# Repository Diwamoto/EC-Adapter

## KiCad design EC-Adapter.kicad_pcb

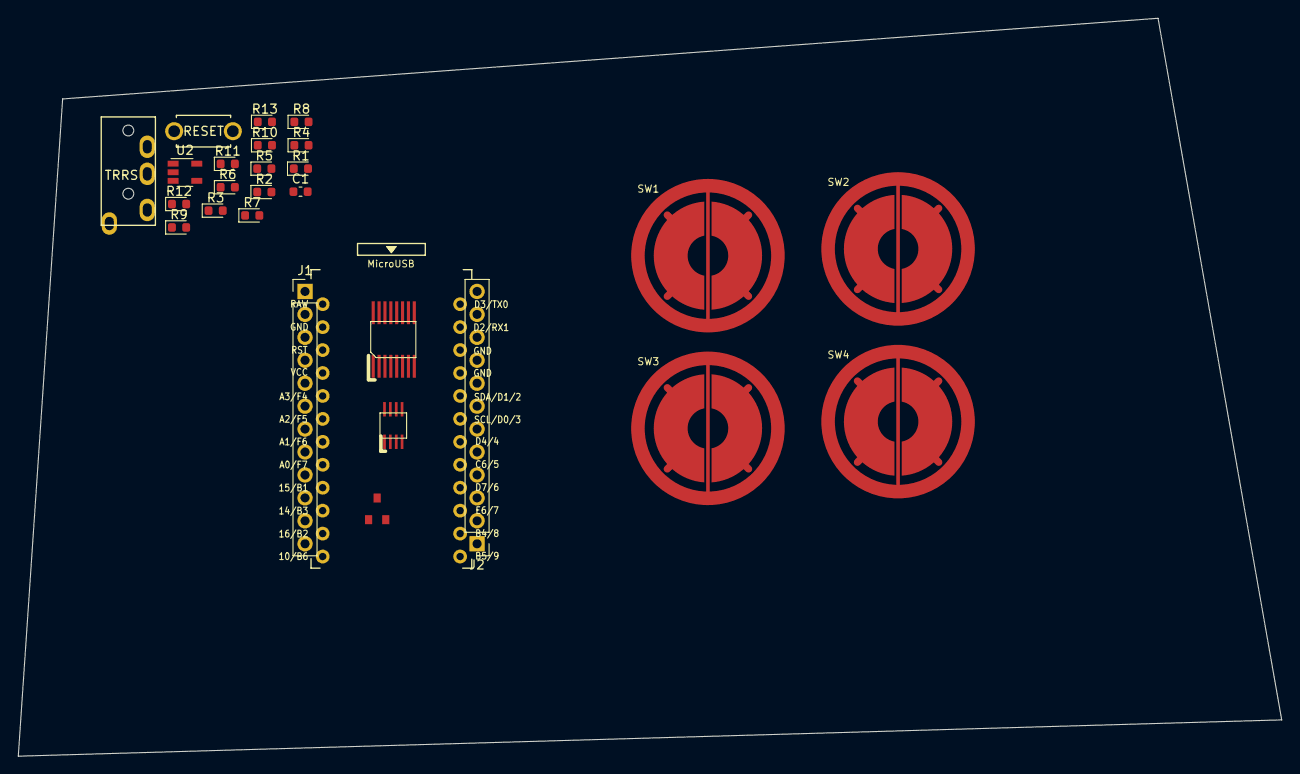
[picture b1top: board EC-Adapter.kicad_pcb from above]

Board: 2 copper layers, 139.9 x 81.7 mm, 27 parts (0 on the bottom side), 24 nets, no tracks yet.

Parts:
C1: 220pF; C_0603_1608Metric
J1, J2: Conn_01x12_Male; PinHeader_1x12_P2.54mm_Vertical
J3: MJ-4PP-9; MJ-4PP-9_1side
Q1: 2SC1941; 2SC2712
R1, R2: 10kΩ; D_0603_1608Metric
R3, R4: 1KΩ; D_0603_1608Metric
R5: 10KΩ; D_0603_1608Metric
R6: 100KΩ; D_0603_1608Metric
R7, R8, R9, R10, R11, R12, R13: 100kΩ; D_0603_1608Metric
SW1: RESET; ResetSW_1side
SW1#2, SW2, SW3, SW4: EC_SW; ec_pad_led2
U1: ProMicro; ProMicro_v3.5
U2: AD8616; TSOT-23-5
U2#2: LTC6228xS6; MSOP8
U3: 74HC4051; SSOP16

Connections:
GND: C1.2, J1.2, J2.9, J2.10, J3.C, Q1.1, R4.1, R7.2, R8.2, R9.2, R10.2, R11.2, R12.2, R13.2, SW1.2, U1.3, U1.4, U1.23, U2.2, U3.4, U3.6, U3.7, U3.8
GNDA: SW1#2.3, SW2.3, SW3.3, SW4.3
unnamed: Q1.2, R2.2
unnamed: Q1.3, R1.2
unnamed: R3.1, U2.3
unnamed: R4.2, R6.2, U2.4
unnamed: R7.1, U3.13
unnamed: R8.1, U3.14
unnamed: R9.1, U3.15
unnamed: R10.1, U3.12
unnamed: R11.1, U3.1
unnamed: R12.1, U3.5
unnamed: R13.1, U3.2
VCC: J1.4, J3.D, R5.2, U1.21, U2.5
a: C1.1, R2.1, R3.2
adc: R5.1, R6.1, U1.13, U2.1
charge: R1.1, U1.14
data: J2.11, J3.B, U1.2
reset: J1.3, SW1.1, U1.22
row0: J2.6, U1.20
row1: J2.5, U1.19
row2: J2.4, U1.18
row3: J2.3, U1.17
row4: J2.2, U1.16

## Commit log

2020-12-29 アップロード（未完成）
2021-02-09 test
